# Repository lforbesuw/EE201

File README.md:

# Replace with Title Here
# EE201

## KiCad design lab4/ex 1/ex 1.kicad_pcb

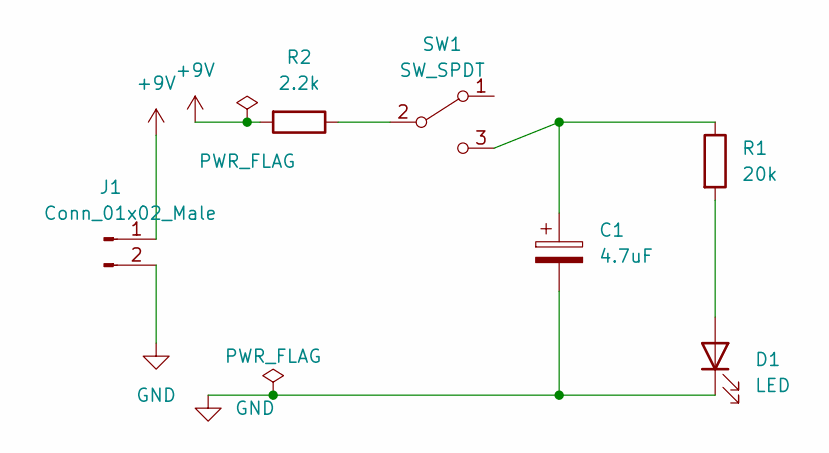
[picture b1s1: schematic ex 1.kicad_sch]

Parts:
C1: 4.7uF; C_Radial_D5.0mm_H5.0mm_P2.00mm
D1: LED; LED_D5.0mm
J1: Conn_01x02_Male; JST_PH_B2B-PH-K_1x02_P2.00mm_Vertical
R1: 20k; R_Axial_DIN0516_L15.5mm_D5.0mm_P20.32mm_Horizontal
R2: 2.2k; R_Axial_DIN0516_L15.5mm_D5.0mm_P20.32mm_Horizontal
SW1: SW_SPDT; SW_E-Switch_EG1224_SPDT_Angled

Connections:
+9V: J1.1, R2.2
GND: C1.2, D1.1 (K), J1.2
unnamed: C1.1, R1.1, SW1.3 (C)
unnamed: D1.2 (A), R1.2
unnamed: R2.1, SW1.2 (B)

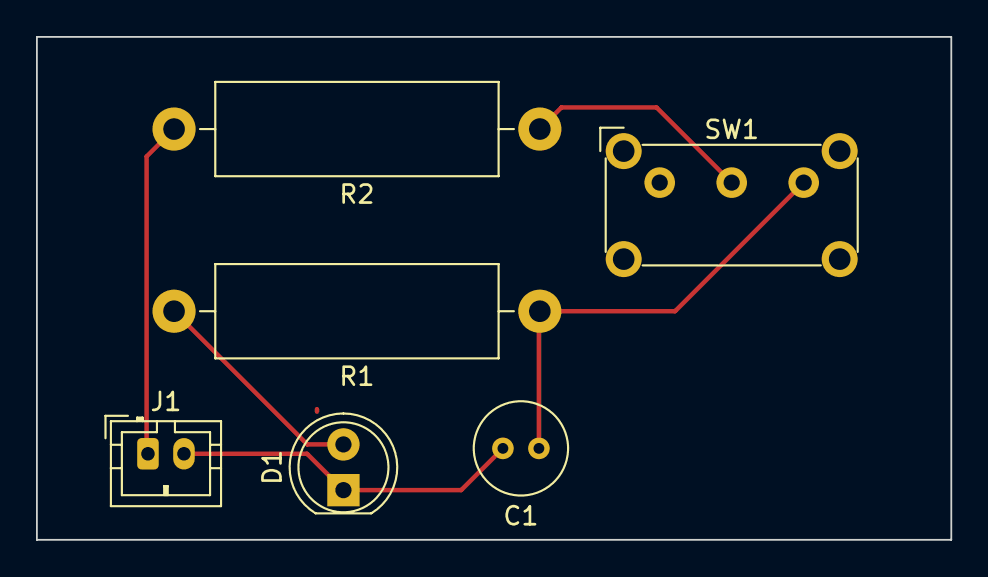
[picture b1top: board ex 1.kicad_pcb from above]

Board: 2 copper layers, 50.8 x 27.9 mm, 6 parts (0 on the bottom side), 5 nets.

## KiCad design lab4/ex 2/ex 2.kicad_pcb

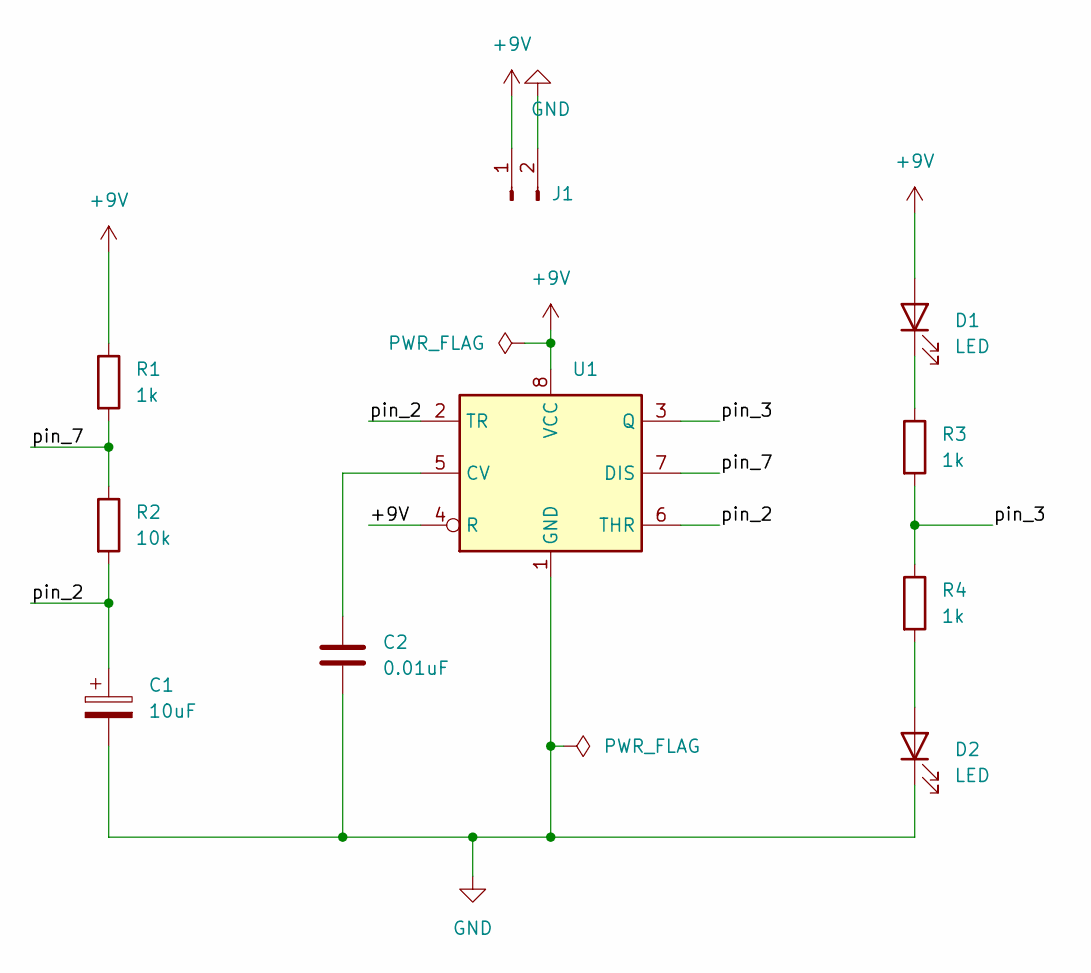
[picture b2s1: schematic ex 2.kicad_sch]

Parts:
C1: 10uF; CP_EIA-3216-18_Kemet-A_Pad1.58x1.35mm_HandSolder
C2: 0.01uF; C_0805_2012Metric_Pad1.18x1.45mm_HandSolder
D1, D2: LED; LED_1206_3216Metric_Pad1.42x1.75mm_HandSolder
J1: Conn_01x02_Male; TerminalBlock_bornier-2_P5.08mm
R1, R3, R4: 1k; R_0805_2012Metric_Pad1.20x1.40mm_HandSolder
R2: 10k; R_0805_2012Metric_Pad1.20x1.40mm_HandSolder
U1: NE555D; SOIC-8-1EP_3.9x4.9mm_P1.27mm_EP2.29x3mm

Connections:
+9V: D1.2 (A), J1.1, R1.1, U1.4 (R), U1.8 (VCC)
/pin_2: C1.1, R2.2, U1.2 (TR), U1.6 (THR)
/pin_3: R3.2, R4.1, U1.3 (Q)
/pin_7: R1.2, R2.1, U1.7 (DIS)
GND: C1.2, C2.2, D2.1 (K), J1.2, U1.1 (GND)
unnamed: C2.1, U1.5 (CV)
unnamed: D1.1 (K), R3.1
unnamed: D2.2 (A), R4.2

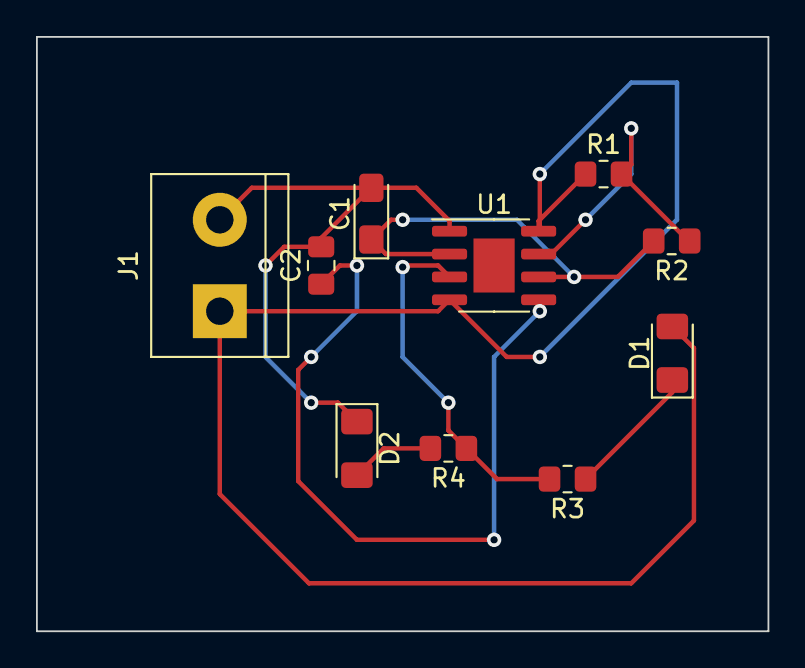
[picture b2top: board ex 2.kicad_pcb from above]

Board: 2 copper layers, 40.6 x 33.0 mm, 10 parts (0 on the bottom side), 8 nets.

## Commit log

2023-01-13 changed the title of readme
2023-01-13 changed the title of readme and added some info
2023-01-14 Changed the title, added more info, added emojis, and end message
2023-01-14 Changed the title and added my name to it
2023-01-27 Added all exercise files
2023-01-27 Added all lab4 exercises
2023-02-03 Added soldering images to Soldering directory
2023-02-10 Updated schematics to include footprints and created a pcb layout
2023-02-17 Added pcb layout screenshot for exercise 1
2023-02-17 Added pcb layout screenshot for exercise 2
2023-03-03 added gerber and drill files for both exercises
